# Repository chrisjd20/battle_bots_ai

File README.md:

# battle_bots_ai

Monorepo for **Plastic Antweight** combat robots (about **1 lb / 454 g or less**) and related work aligned with **SPARC** (Standardized Procedures for the Advancement of Robotic Combat). It holds software, PCB design, mechanical/CAD, 3D-printed parts, and docs for **multiple** bots and battle-bot accessories—not a single project.

## PCB design

**KiCad** is used for all PCB work. Shared footprints/symbols can live under `shared/kicad-libraries/`; per-bot or per-accessory boards sit under `bots/<name>/` or `accessories/<name>/` (often in a `pcb/` subfolder as projects grow).

`launch.sh` can open a KiCad project when present (see script for the expected path).

## KiCad + AI setup

- MCP config: `.cursor/mcp.json` (server name `kicad`)
- Launcher: `./launch.sh` (auto-detects one project, or pass explicit `.kicad_pro`)
- Workflow guide: `docs/hardware-workflow.md`
- Fabrication output location: `fab/`

Quick commands (after a KiCad project exists):

```bash
./launch.sh --check path/to/project.kicad_pro
kicad-cli sch erc path/to/project.kicad_sch
kicad-cli pcb drc path/to/project.kicad_pcb
```

## Mechanical CAD + AI setup

- Primary tooling: `FreeCAD` (GUI) + `build123d`/`CadQuery` (Python source)
- CAD tool bootstrap: `./shared/software-tools/cad/bootstrap.sh`
- MCP config: `.cursor/mcp.json` (server name `cad`)
- CAD workflow notes: `shared/software-tools/cad/README.md`

Quick commands:

```bash
./shared/software-tools/cad/bootstrap.sh
.venv-cad/bin/python bots/flipping-cool/cad/src/baseline_layout.py
```

## Repo layout (starter)

| Path | Purpose |
|------|---------|
| `bots/` | One folder per robot |
| `accessories/` | Tools, jigs, side projects, non-robot-specific hardware |
| `shared/kicad-libraries/` | Reusable KiCad symbols, footprints, 3D models |
| `shared/cad-templates/` | Reusable CAD starter files or templates |
| `shared/software-tools/` | Shared scripts, utilities, or small tools |
| `docs/reference/` | Rules, datasheets summaries, reference notes |
| `docs/build-notes/` | Build logs, BOMs, assembly notes |

Individual projects may add subfolders such as `pcb/`, `firmware/`, `software/`, `cad/`, `prints/`, and `docs/` as needed.

## Other docs

- Design notes and concepts: keep them inside each bot's `docs/` folder (example: `bots/flipping-cool/docs/`).

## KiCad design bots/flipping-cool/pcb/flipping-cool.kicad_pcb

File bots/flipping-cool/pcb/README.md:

# Flipping Cool Rev B PCB

This KiCad project is now the active Rev B integration target for
`flipping-cool`. Rev A remains the historical receiver-driven baseline in the
older schematic sheets and docs; Rev B is the aggressive single-board control
and power architecture.

## Rev B Intent

Rev B integrates the electronics that make sense to put on the robot PCB:

- ESP32-S3-WROOM-1 module for firmware, BLE alternate control, telemetry, ADC
  rail sensing, status LEDs, I2C, and CRSF experiments.
- Board-generated `SERVO_6V` rail with a 5.5 A minimum target for receiver and
  weapon servo loads.
- Board-generated `AUX_3V3` rail for MCU, sensors, status, and debug logic.
- Hardware authority selection using the mandatory user-facing
  `SAFE / RX_DIRECT / MCU_CONTROL` switch.
- Receiver-priority PWM routing through hardware mux footprints so
  `RX_DIRECT` can bypass an unpowered or failed MCU.
- Matek receiver interface, optional CRSF UART, WEKA-native ESC power/PWM
  interface, motor/servo harness connectors, ADC dividers, debug headers, I2C,
  and status LEDs.

These remain off-board by design: motors, weapon servos, battery pack, WEKA
ESC, and Matek receiver.

## Active Artifacts

- `build_rev_b_pcb.py`: reproducible Rev B PCB/fab generator.
- `flipping-cool.kicad_pcb`: generated Rev B active board target, about
  `120 x 100 mm`, 4 copper layers.
- `fab_rev_b/`: generated Gerbers, drill, position CSV, STEP, renders, ZIP,
  and DRC report.
- `../docs/rev_b_architecture.md`: Rev B architecture and bench validation
  contract.

Run the generator from the repo root:

```bash
python3 bots/flipping-cool/pcb/build_rev_b_pcb.py
```

Run PCB DRC:

```bash
kicad-cli pcb drc bots/flipping-cool/pcb/flipping-cool.kicad_pcb \
  --output bots/flipping-cool/pcb/fab_rev_b/flipping-cool-rev-b-drc.rpt \
  --format report
```

## Current Validation Status

Rev B is **not yet print-ready**. The generated board/fab package exists, but
KiCad DRC is still failing in `fab_rev_b/flipping-cool-rev-b-drc.rpt`.

Current blocker class:

- Generated routing still needs hand/interactive cleanup around the ESP32-S3,
  switch/mux cluster, headers, and high-current rails.
- The schematic intent and board architecture are present, but PCB DRC must be
  driven to zero errors before ordering.

Acceptance remains:

- ERC: zero errors.
- PCB DRC: zero errors and zero required unconnected items.
- Rev B footprints present for MCU, regulators, mode switch, muxes, receiver,
  CRSF, WEKA interfaces, servo outputs, sensing, debug, I2C, and status.
- Fab ZIP regenerated only after DRC is clean.

Do not fabricate Rev B until DRC passes.

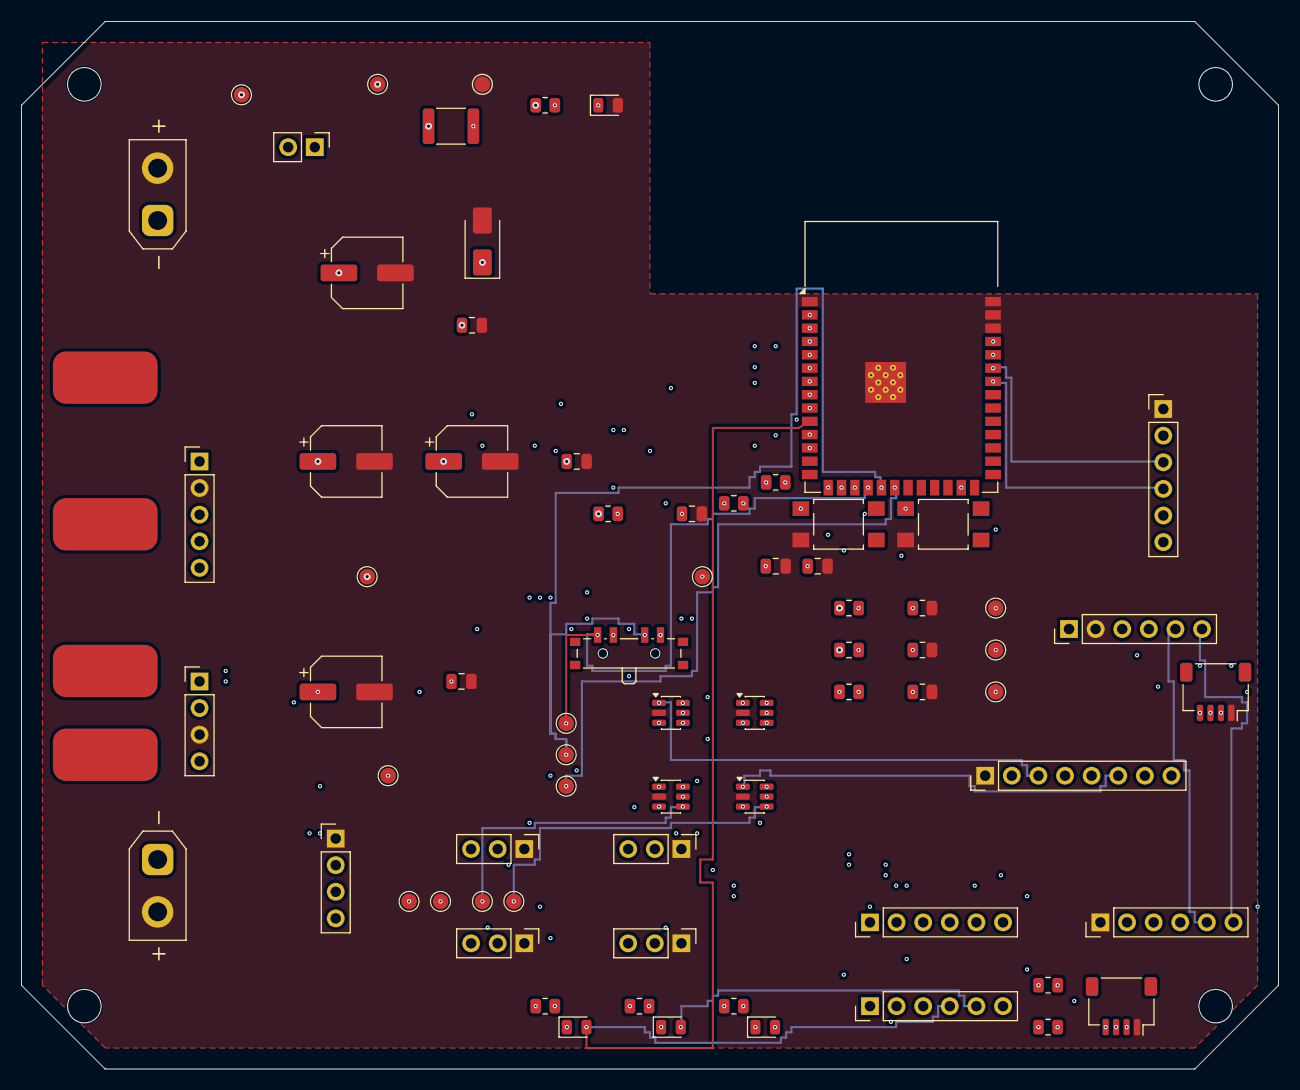
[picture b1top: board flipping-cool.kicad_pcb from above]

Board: 4 copper layers, 120.0 x 100.0 mm, 81 parts (0 on the bottom side), 42 nets.

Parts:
C1: 470uF_16V_LOW_ESR; CP_Elec_6.3x7.7
C2: 10uF_16V; C_0805_2012Metric
C10: 10uF_3V3_LOCAL; C_0805_2012Metric
C11: 100nF_3V3_LOCAL; C_0805_2012Metric
C20: 1000uF_10V_SERVO; CP_Elec_6.3x7.7
C21: 100uF_10V; CP_Elec_6.3x7.7
C22: 10uF_10V; C_0805_2012Metric
C23: 22uF_RX; C_0805_2012Metric
C30: 47uF_6V3; CP_Elec_6.3x7.7
C31: 10uF_6V3; C_0805_2012Metric
D1: SMBJ12CA_TVS; D_SMA
D2: PWR_LED; LED_0805_2012Metric
D50, D51, D52: STATUS_LED; LED_0805_2012Metric
F1: PTC_500mA_AUX; Fuse_1812_4532Metric
FB1: RX_6V_FILTER; R_0805_2012Metric
J1: BATTERY_XT30; AMASS_XT30UPB-F_1x02_P5.0mm_Vertical
J2: REMOVE_LINK_VBAT; PinHeader_1x02_P2.54mm_Vertical
J10: MATEK_ELRS_R24_P6_PWM; PinHeader_1x08_P2.54mm_Vertical
J11: CRSF_UART; JST_SH_SM04B-SRSS-TB_1x04-1MP_P1.00mm_Horizontal
J12: UART_PROGRAM; PinHeader_1x06_P2.54mm_Vertical
J20: WEKA_POWER_XT30; AMASS_XT30UPB-F_1x02_P5.0mm_Vertical
J21: WEKA_PWM; PinHeader_1x04_P2.54mm_Vertical
J23: WEKA_M1A; SolderWirePad_1x01_SMD_5x10mm
J24: WEKA_M1B; SolderWirePad_1x01_SMD_5x10mm
J25: WEKA_M2A; SolderWirePad_1x01_SMD_5x10mm
J26: WEKA_M2B; SolderWirePad_1x01_SMD_5x10mm
J30: PWM_WEAPON_FR_SERVO; PinHeader_1x03_P2.54mm_Vertical
J31: PWM_WEAPON_LR_SERVO; PinHeader_1x03_P2.54mm_Vertical
J32: PWM_SERVO_SPARE1_SERVO; PinHeader_1x03_P2.54mm_Vertical
J33: PWM_SERVO_SPARE2_SERVO; PinHeader_1x03_P2.54mm_Vertical
J44: PIT_DEBUG; PinHeader_1x06_P2.54mm_Vertical
J46: MCU_POWER_COMMS; PinHeader_1x06_P2.54mm_Vertical
J47: MCU_SIGNAL_TAPS; PinHeader_1x06_P2.54mm_Vertical
J48: MCU_SENSE_STATUS; PinHeader_1x06_P2.54mm_Vertical
J49: I2C_STEMMA_QT; JST_SH_SM04B-SRSS-TB_1x04-1MP_P1.00mm_Horizontal
MH1, MH2, MH3, MH4: M3 mounting; MountingHole_3.2mm_M3
R1: 2.2k; R_0805_2012Metric
R10: 10k_EN_PULLUP; R_0805_2012Metric
R11: 10k_BOOT_PULLUP; R_0805_2012Metric
R40, R42, R44: 100k; R_0805_2012Metric
R41, R43, R45: 47k; R_0805_2012Metric
R46, R47: 4.7k_DNP; R_0805_2012Metric
R50, R51, R52: 330; R_0805_2012Metric
SW1: MODE_SAFE_RX_MCU; SW_SP3T_PCM13
SW2: RESET; SW_SPST_TL3305B
SW3: BOOT; SW_SPST_TL3305B
TP1: VBAT_RAW; TestPoint_Pad_D1.5mm
TP2: VBAT_SW; TestPoint_Pad_D1.5mm
TP3: GND; TestPoint_Pad_D1.5mm
TP4: SERVO_6V; TestPoint_Pad_D1.5mm
TP5: RX_6V; TestPoint_Pad_D1.5mm
TP6: AUX_3V3; TestPoint_Pad_D1.5mm
TP7: MODE_SAFE; TestPoint_Pad_D1.5mm
TP8: MODE_RX_DIRECT; TestPoint_Pad_D1.5mm
TP9: MODE_MCU_CONTROL; TestPoint_Pad_D1.5mm
TP10: ADC_VBAT; TestPoint_Pad_D1.5mm
TP11: ADC_SERVO_6V; TestPoint_Pad_D1.5mm
TP12: ADC_RX_6V; TestPoint_Pad_D1.5mm
TP13: PWM_DRIVE_LEFT; TestPoint_Pad_D1.5mm
TP14: PWM_DRIVE_RIGHT; TestPoint_Pad_D1.5mm
TP15: PWM_WEAPON_FR; TestPoint_Pad_D1.5mm
TP16: PWM_WEAPON_LR; TestPoint_Pad_D1.5mm
U10: ESP32-S3-WROOM-1
U20: 6V_BUCK_5.5A_MIN; PinHeader_1x05_P2.54mm_Vertical
U30: 3V3_BUCK_POL_D24V5F3; PinHeader_1x04_P2.54mm_Vertical
U40: SPDT_PWM_MUX_PWM_DRIVE_LEFT; SOT-23-6
U41: SPDT_PWM_MUX_PWM_DRIVE_RIGHT; SOT-23-6
U42: SPDT_PWM_MUX_PWM_WEAPON_FR; SOT-23-6
U43: SPDT_PWM_MUX_PWM_WEAPON_LR; SOT-23-6

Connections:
ADC_RX_6V: J48.3, R44.2, R45.1, TP12.1, U10.17
ADC_SERVO_6V: J48.2, R42.2, R43.1, TP11.1, U10.16
ADC_VBAT: J48.1, R40.2, R41.1, TP10.1, U10.15
AUX_3V3: C10.1, C11.1, C30.1, C31.1, J12.2, J46.2, J49.2, R10.1, R11.1, R46.1, R47.1, R50.1, R51.1, R52.1, SW1.2, TP6.1, U10.2, U30.4, U40.6, U41.6, U42.6, U43.6
AUX_3V3_SHDN: J46.4, U30.1
BUCK6_PG: J46.3, U20.5
CRSF_RX_FROM_RX: J11.3, J44.6, J46.6, U10.36
CRSF_TX_TO_RX: J11.4, J44.5, J46.5, U10.37
ESP_BOOT: J12.6, R11.2, SW3.1, U10.25
ESP_EN: J12.5, R10.2, SW2.1, U10.3
GND_PWR: C1.2, C2.2, C10.2, C11.2, C20.2, C21.2, C22.2, C23.2, C30.2, C31.2, D1.2, D2.2, J1.2, J10.1, J11.1, J12.1, J20.2, J21.1, J30.1, J31.1, J32.1, J33.1, J44.2, J46.1, J49.1, R41.2, R43.2, R45.2, SW2.2, SW3.2, TP3.1, U10.1, U10.38, U10.39, U10.40, U10.41, U20.2, U30.3, U40.2, U41.2, U42.2, U43.2
I2C_SCL: J47.2, J49.4, R47.2, U10.9
I2C_SDA: J47.1, J49.3, R46.2, U10.8
MCU_PWM_DRIVE_LEFT: U10.4, U40.3
MCU_PWM_DRIVE_RIGHT: U10.5, U41.3
MCU_PWM_WEAPON_FR: U10.6, U42.3
MCU_PWM_WEAPON_LR: U10.7, U43.3
MODE_MCU_CONTROL: SW1.4, TP9.1, U10.20, U40.5, U41.5, U42.5, U43.5
MODE_RX_DIRECT: SW1.3, TP8.1, U10.19
MODE_SAFE: SW1.1, TP7.1, U10.18
PWM_DRIVE_LEFT: J21.3, J47.3, TP13.1, U40.4
PWM_DRIVE_RIGHT: J21.4, J47.4, TP14.1, U41.4
PWM_WEAPON_FR: J30.3, J47.5, TP15.1, U42.4
PWM_WEAPON_LR: J31.3, J47.6, TP16.1, U43.4
PWR_LED_A: D2.1, R1.2
RX_6V: C23.1, FB1.2, J10.2, J11.2, J44.4, R44.1, TP5.1
RX_PWM_DRIVE_LEFT: J10.3, U40.1
RX_PWM_DRIVE_RIGHT: J10.4, U41.1
RX_PWM_WEAPON_FR: J10.5, U42.1
RX_PWM_WEAPON_LR: J10.6, U43.1
SERVO_6V: C20.1, C21.1, C22.1, FB1.1, J30.2, J31.2, J32.2, J33.2, J44.3, R42.1, TP4.1, U20.3
STATUS_LED_B_A: D52.1, R52.2
STATUS_LED_B_N: D52.2, J48.6, U10.12
STATUS_LED_G_A: D51.1, R51.2
STATUS_LED_G_N: D51.2, J48.5, U10.11
STATUS_LED_R_A: D50.1, R50.2
STATUS_LED_R_N: D50.2, J48.4, U10.10
UART0_RXD: J12.4, U10.34
UART0_TXD: J12.3, U10.35
VBAT_RAW: J1.1, J2.1, TP1.1
VBAT_SW: C1.1, C2.1, D1.1, F1.1, J2.2, J20.1, J44.1, R1.1, R40.1, TP2.1, U20.1
VBAT_SW_FUSED: F1.2, U30.2

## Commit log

2026-04-18 Update README.md to include specifications for Plastic Antweights (1lb to 454g) and SPARC guidelines.
2026-04-18 Enhance BATTLE_BOT1.md with detailed design recommendations for a 1 lb control flipper, emphasizing weight optimization, weapon configuration, and drive system improvements. Update README.md to clari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
2026-04-18 Remove BATTLE_BOT1.md as it is no longer needed. Update README.md to reflect the new documentation structure, directing users to keep design notes within each bot's `docs/` folder.
2026-04-19 Update documentation to include mechanical CAD setup instructions and enhance KiCad workflow guidelines. Add local Python virtual environment entries to .gitignore and configure MCP for CAD operation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
2026-05-09 Update README.md to clarify current scripts for generating layouts and add instructions for viewing in FreeCAD. Enhance BOM.md with optional electrical growth parts and their specifications for futur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
2026-05-09 Update ERC report timestamp to reflect the latest generation time.
2026-05-09 Enhance KiCad project configuration by adding detailed design settings, including default parameters, rule severities, and teardrop options. Update track widths and via dimensions for improved layout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
2026-05-09 Refactor KiCad PCB design by reorganizing net connections, adding a new mounting hole footprint, and updating existing footprints for resistors and test points. Adjust design rules in the project con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
2026-05-09 Update KiCad PCB design by renaming footprints for resistors, capacitors, connectors, and test points to include component categories. Adjust footprint positions for improved layout accuracy and cons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
2026-05-09 Refactor Flipping Cool PCB design to Rev B, integrating active electrical features including ESP32-S3 module, power management, and control authority. Update documentation to reflect new architecture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
2026-05-09 Refactor Flipping Cool PCB design to Rev B, updating title, date, and revision details. Integrate ESP32-S3 module and enhance documentation for MCU I/O and debugging features, while maintaining histo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
2026-05-09 Remove obsolete Flipping Cool Rev B project plan file and update schematic files to reflect the latest design changes, including integration of the ESP32-S3 module and enhancements to power managemen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
